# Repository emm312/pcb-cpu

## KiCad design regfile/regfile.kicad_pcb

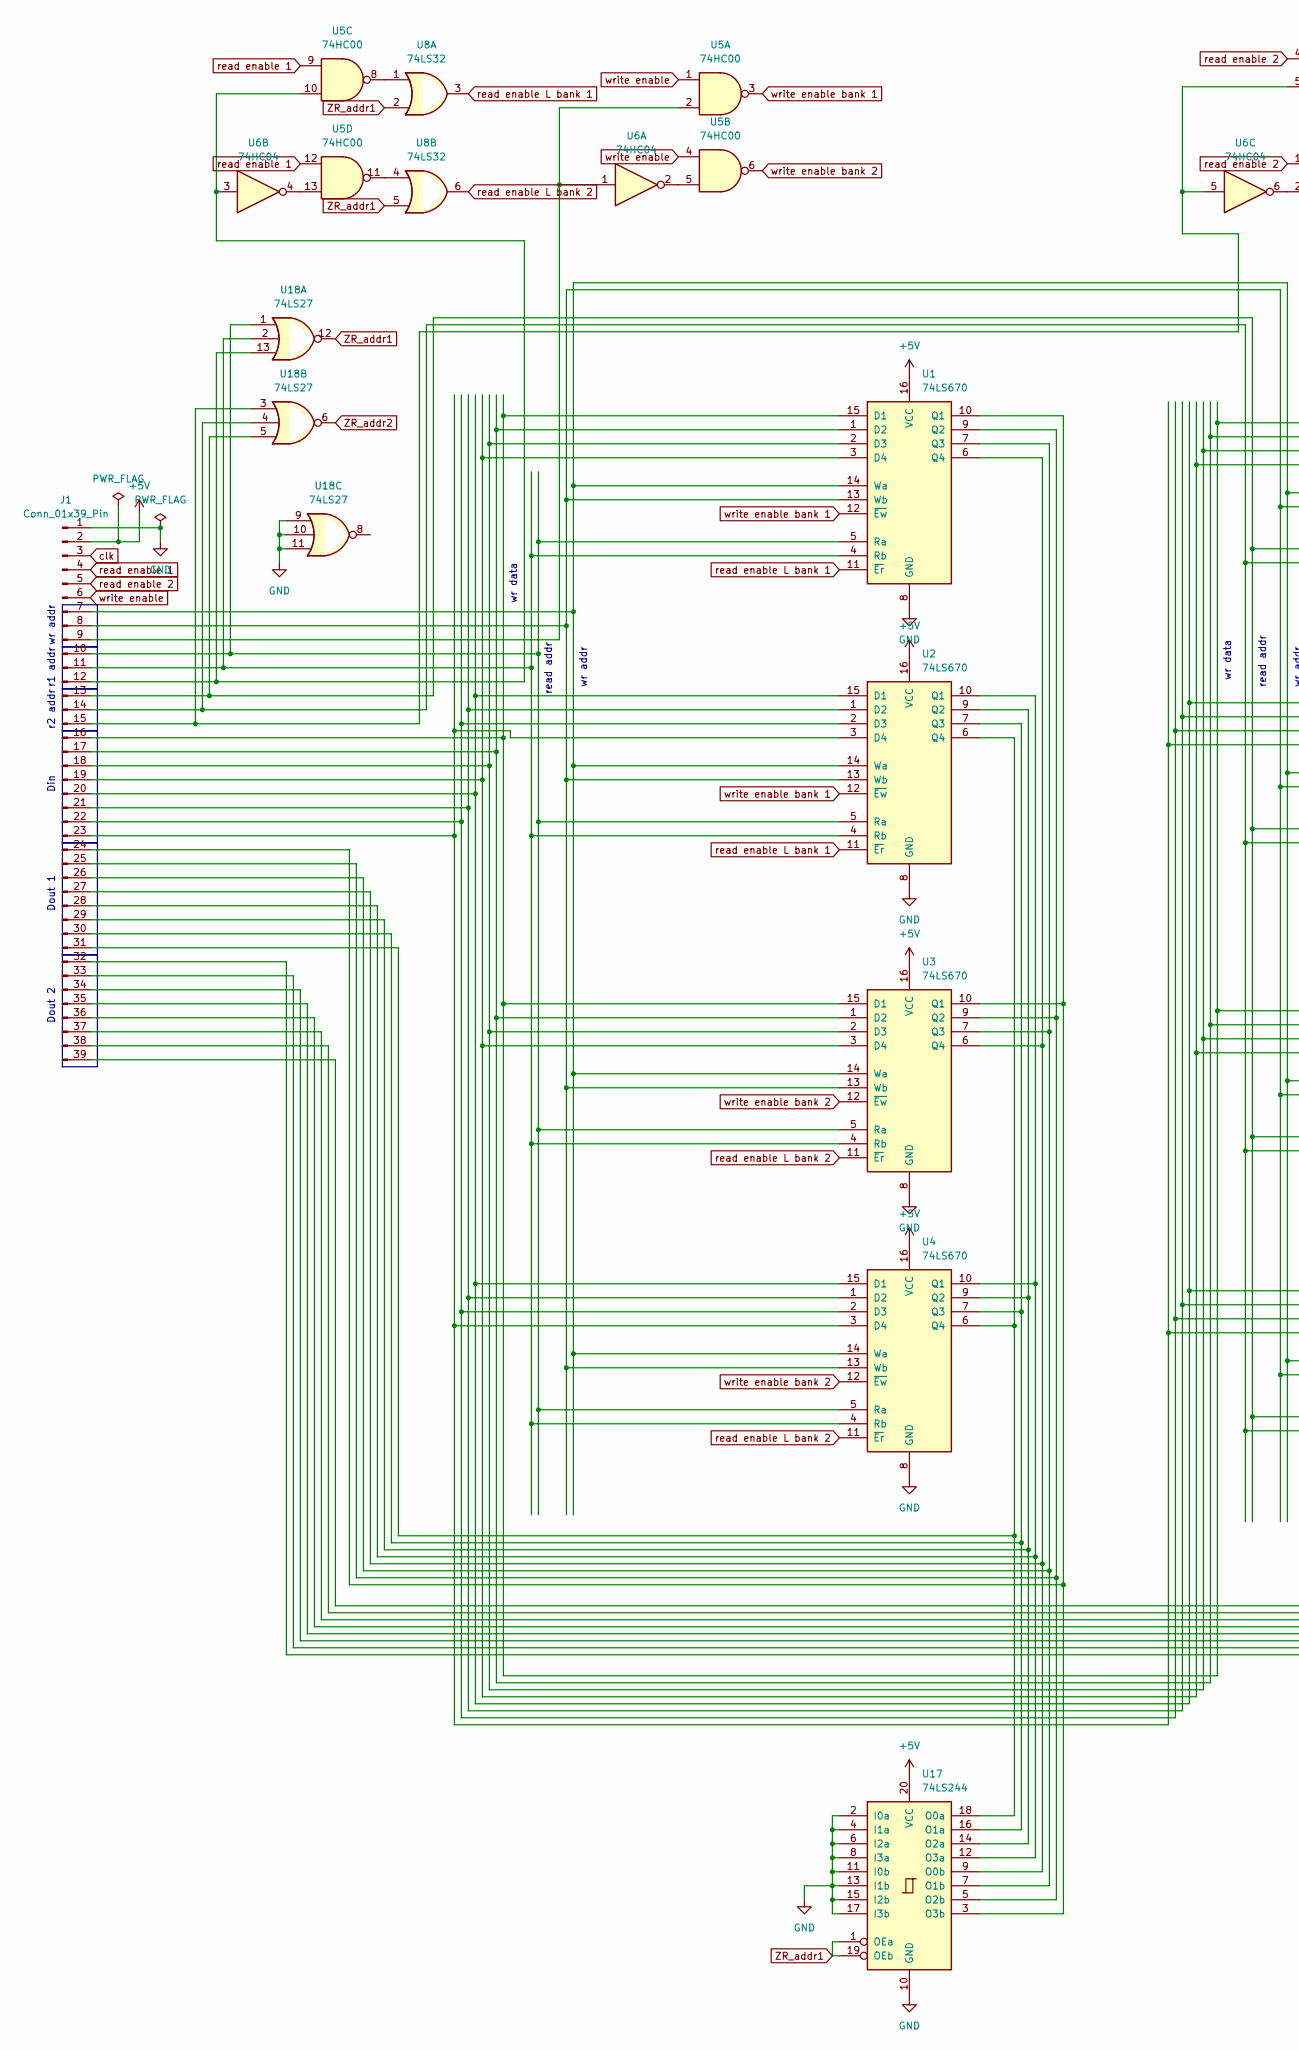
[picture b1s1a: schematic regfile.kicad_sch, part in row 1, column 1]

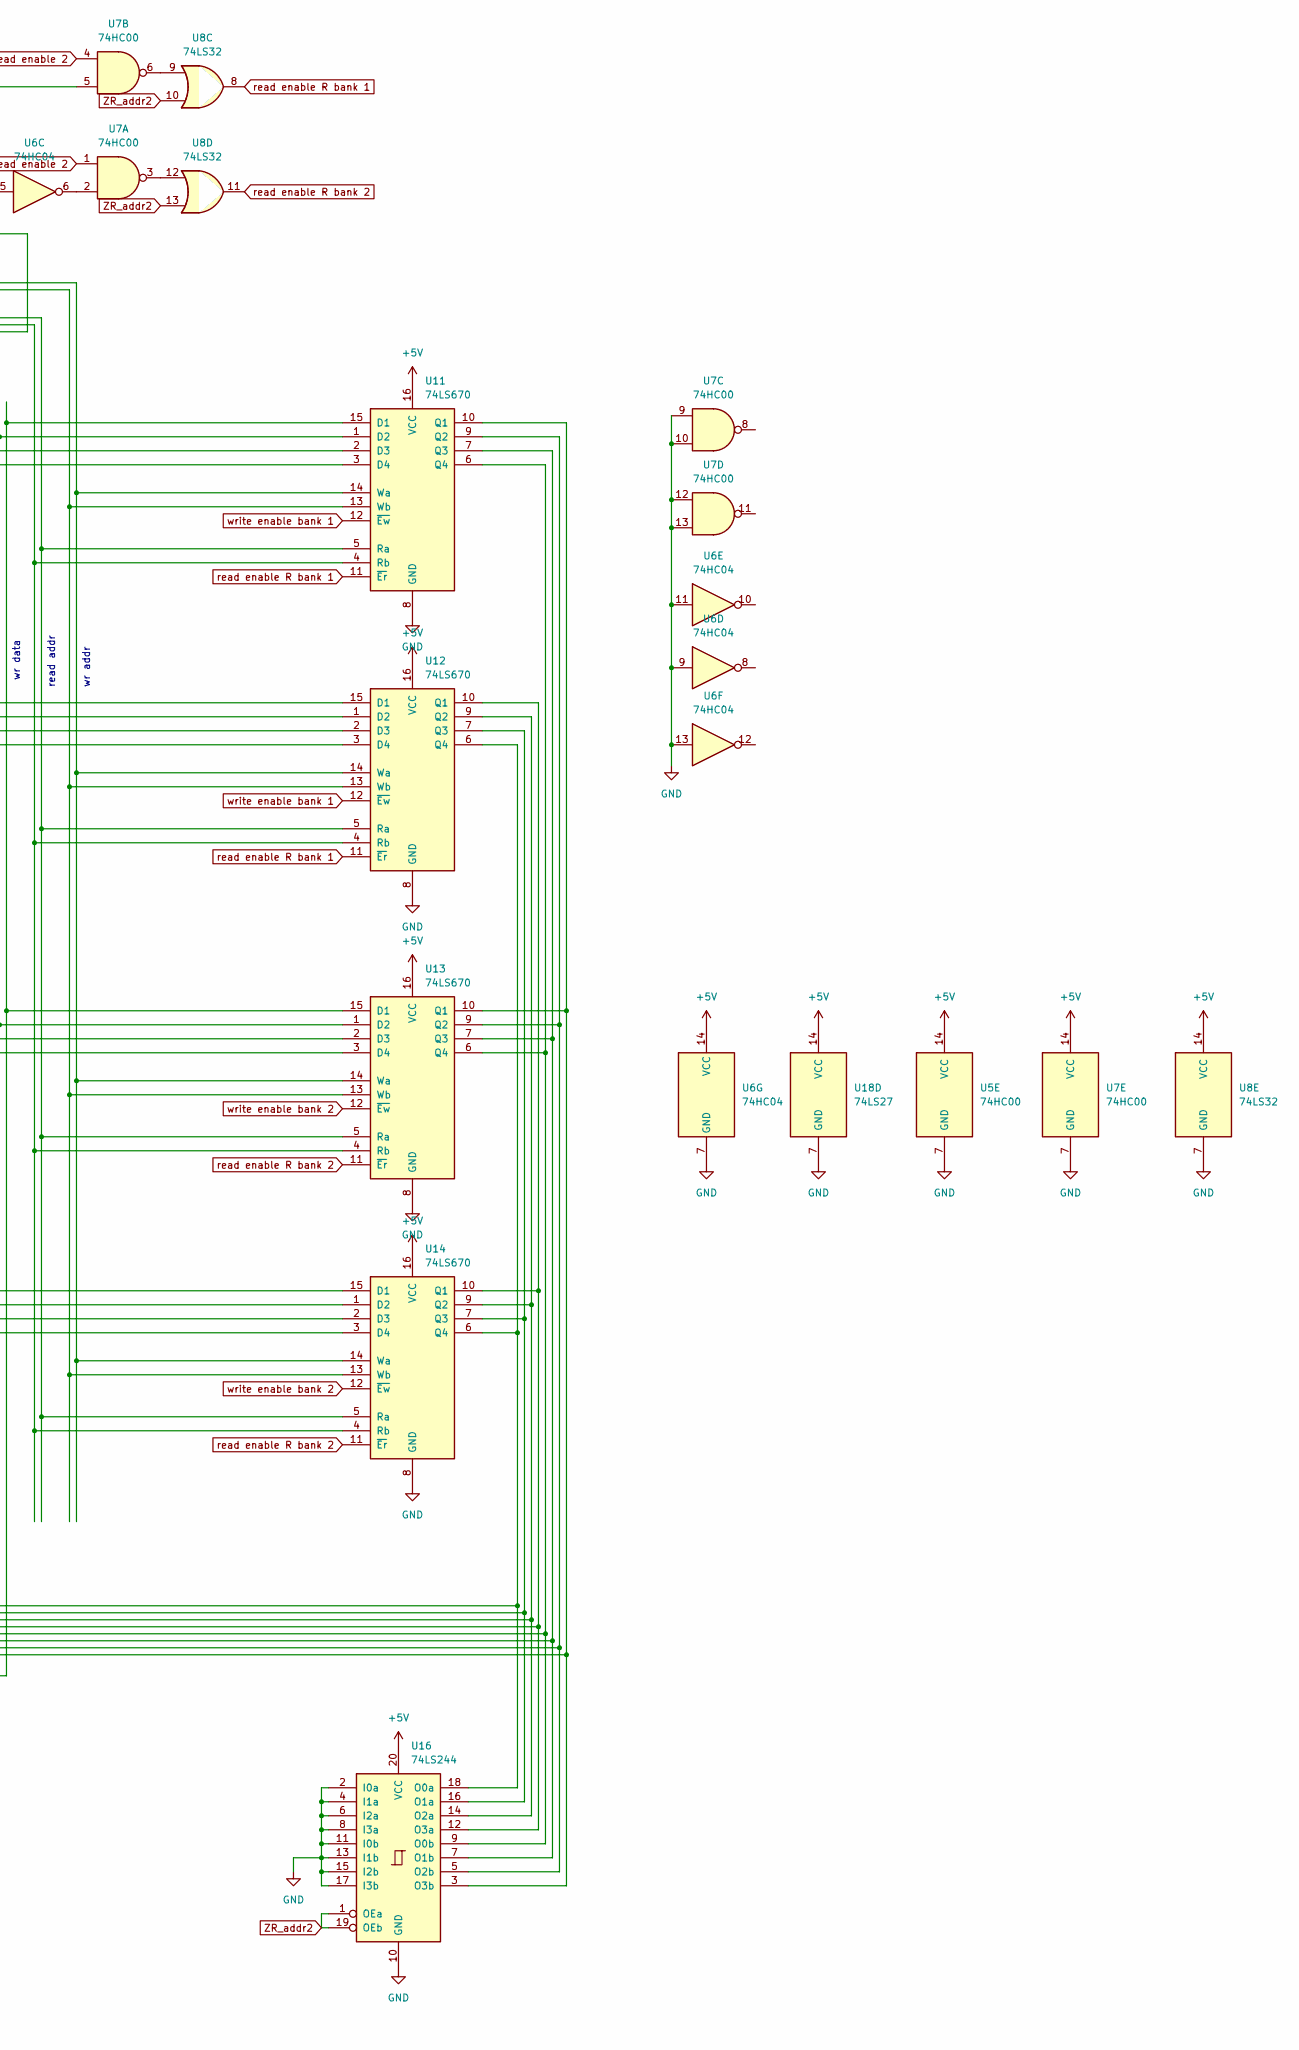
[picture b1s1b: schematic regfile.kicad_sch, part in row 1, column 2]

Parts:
J1: Conn_01x39_Pin; PinHeader_1x39_P2.54mm_Horizontal
U1, U2, U3, U4, U11, U12, U13, U14: 74LS670; DIP-16_W7.62mm
U5, U7: 74HC00; DIP-14_W7.62mm
U6: 74HC04; DIP-14_W7.62mm
U8: 74LS32; DIP-14_W7.62mm
U16, U17: 74LS244; DIP-20_W7.62mm
U18: 74LS27; DIP-14_W7.62mm

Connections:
+5V: J1.2, U1.16 (VCC), U2.16 (VCC), U3.16 (VCC), U4.16 (VCC), U5.14 (VCC), U6.14 (VCC), U7.14 (VCC), U8.14 (VCC), U11.16 (VCC), U12.16 (VCC), U13.16 (VCC), U14.16 (VCC), U16.20 (VCC), U17.20 (VCC), U18.14 (VCC)
GND: J1.1, U1.8 (GND), U2.8 (GND), U3.8 (GND), U4.8 (GND), U5.7 (GND), U6.7 (GND), U6.9, U6.11, U6.13, U7.7 (GND), U7.9, U7.10, U7.12, U7.13, U8.7 (GND), U11.8 (GND), U12.8 (GND), U13.8 (GND), U14.8 (GND), U16.2 (I0a), U16.4 (I1a), U16.6 (I2a), U16.8 (I3a), U16.10 (GND), U16.11 (I0b), U16.13 (I1b), U16.15 (I2b), U16.17 (I3b), U17.2 (I0a), U17.4 (I1a), U17.6 (I2a), U17.8 (I3a), U17.10 (GND), U17.11 (I0b), U17.13 (I1b), U17.15 (I2b), U17.17 (I3b), U18.7 (GND), U18.9, U18.10, U18.11
unnamed: J1.7, U1.14 (Wa), U2.14 (Wa), U3.14 (Wa), U4.14 (Wa), U11.14 (Wa), U12.14 (Wa), U13.14 (Wa), U14.14 (Wa)
unnamed: J1.8, U1.13 (Wb), U2.13 (Wb), U3.13 (Wb), U4.13 (Wb), U11.13 (Wb), U12.13 (Wb), U13.13 (Wb), U14.13 (Wb)
unnamed: J1.9, U5.2, U6.1
unnamed: J1.10, U1.5 (Ra), U2.5 (Ra), U3.5 (Ra), U4.5 (Ra), U18.1
unnamed: J1.11, U1.4 (Rb), U2.4 (Rb), U3.4 (Rb), U4.4 (Rb), U18.2
unnamed: J1.12, U5.10, U6.3, U18.13
unnamed: J1.13, U11.5 (Ra), U12.5 (Ra), U13.5 (Ra), U14.5 (Ra), U18.5
unnamed: J1.14, U11.4 (Rb), U12.4 (Rb), U13.4 (Rb), U14.4 (Rb), U18.4
unnamed: J1.15, U6.5, U7.5, U18.3
unnamed: J1.16, U1.15 (D1), U3.15 (D1), U11.15 (D1), U13.15 (D1)
unnamed: J1.17, U1.1 (D2), U3.1 (D2), U11.1 (D2), U13.1 (D2)
unnamed: J1.18, U1.2 (D3), U3.2 (D3), U11.2 (D3), U13.2 (D3)
unnamed: J1.19, U1.3 (D4), U3.3 (D4), U11.3 (D4), U13.3 (D4)
unnamed: J1.20, U2.15 (D1), U4.15 (D1), U12.15 (D1), U14.15 (D1)
unnamed: J1.21, U2.1 (D2), U4.1 (D2), U12.1 (D2), U14.1 (D2)
unnamed: J1.22, U2.2 (D3), U4.2 (D3), U12.2 (D3), U14.2 (D3)
unnamed: J1.23, U2.3 (D4), U4.3 (D4), U12.3 (D4), U14.3 (D4)
unnamed: J1.24, U1.10 (Q1), U3.10 (Q1), U17.3 (O3b)
unnamed: J1.25, U1.9 (Q2), U3.9 (Q2), U17.5 (O2b)
unnamed: J1.26, U1.7 (Q3), U3.7 (Q3), U17.7 (O1b)
unnamed: J1.27, U1.6 (Q4), U3.6 (Q4), U17.9 (O0b)
unnamed: J1.28, U2.10 (Q1), U4.10 (Q1), U17.12 (O3a)
unnamed: J1.29, U2.9 (Q2), U4.9 (Q2), U17.14 (O2a)
unnamed: J1.30, U2.7 (Q3), U4.7 (Q3), U17.16 (O1a)
unnamed: J1.31, U2.6 (Q4), U4.6 (Q4), U17.18 (O0a)
unnamed: J1.32, U11.10 (Q1), U13.10 (Q1), U16.3 (O3b)
unnamed: J1.33, U11.9 (Q2), U13.9 (Q2), U16.5 (O2b)
unnamed: J1.34, U11.7 (Q3), U13.7 (Q3), U16.7 (O1b)
unnamed: J1.35, U11.6 (Q4), U13.6 (Q4), U16.9 (O0b)
unnamed: J1.36, U12.10 (Q1), U14.10 (Q1), U16.12 (O3a)
unnamed: J1.37, U12.9 (Q2), U14.9 (Q2), U16.14 (O2a)
unnamed: J1.38, U12.7 (Q3), U14.7 (Q3), U16.16 (O1a)
unnamed: J1.39, U12.6 (Q4), U14.6 (Q4), U16.18 (O0a)
unnamed: U5.5, U6.2
unnamed: U5.8, U8.1
unnamed: U5.11, U8.4
unnamed: U5.13, U6.4
unnamed: U6.6, U7.2
unnamed: U7.3, U8.12
unnamed: U7.6, U8.9
ZR_addr1: U8.2, U8.5, U17.1 (OEa), U17.19 (OEb), U18.12
ZR_addr2: U8.10, U8.13, U16.1 (OEa), U16.19 (OEb), U18.6
clk: J1.3
read enable 1: J1.4, U5.9, U5.12
read enable 2: J1.5, U7.1, U7.4
read enable L bank 1: U1.11 (~Er), U2.11 (~Er), U8.3
read enable L bank 2: U3.11 (~Er), U4.11 (~Er), U8.6
read enable R bank 1: U8.8, U11.11 (~Er), U12.11 (~Er)
read enable R bank 2: U8.11, U13.11 (~Er), U14.11 (~Er)
write enable: J1.6, U5.1, U5.4
write enable bank 1: U1.12 (~Ew), U2.12 (~Ew), U5.3, U11.12 (~Ew), U12.12 (~Ew)
write enable bank 2: U3.12 (~Ew), U4.12 (~Ew), U5.6, U13.12 (~Ew), U14.12 (~Ew)

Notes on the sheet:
Dout 1
Din
Dout 2
read addr
wr addr
r2 addr
wr data
r1 addr

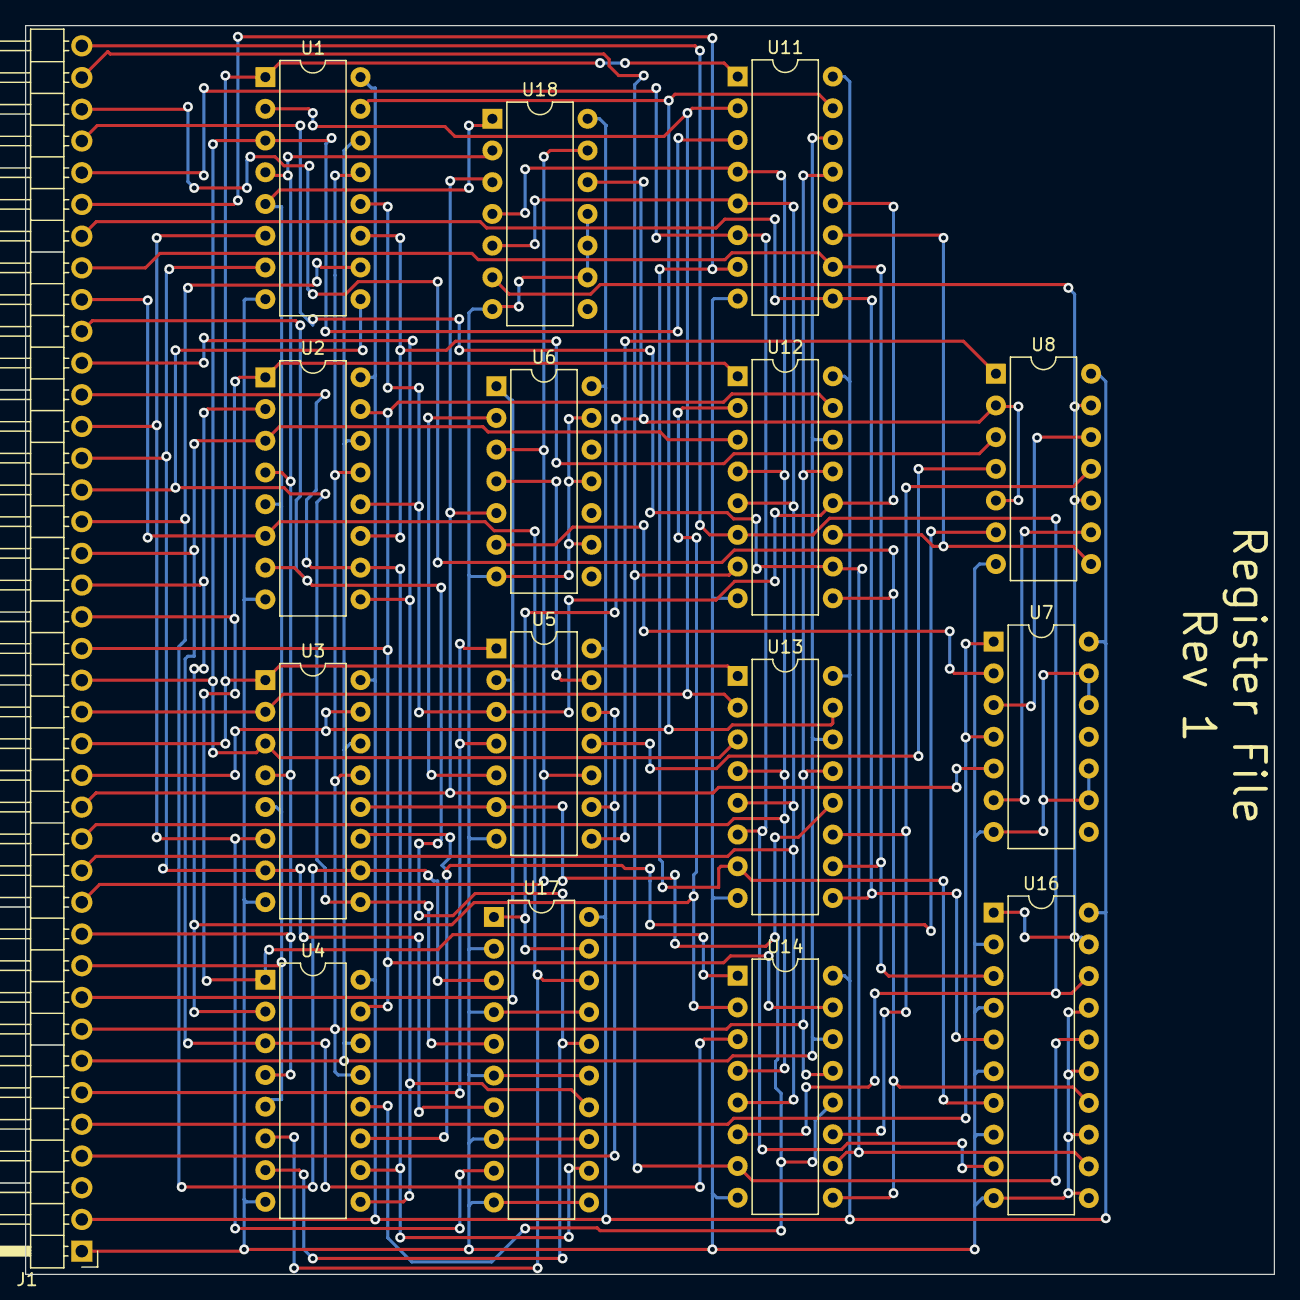
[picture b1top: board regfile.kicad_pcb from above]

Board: 2 copper layers, 100.0 x 100.0 mm, 16 parts (0 on the bottom side), 53 nets.

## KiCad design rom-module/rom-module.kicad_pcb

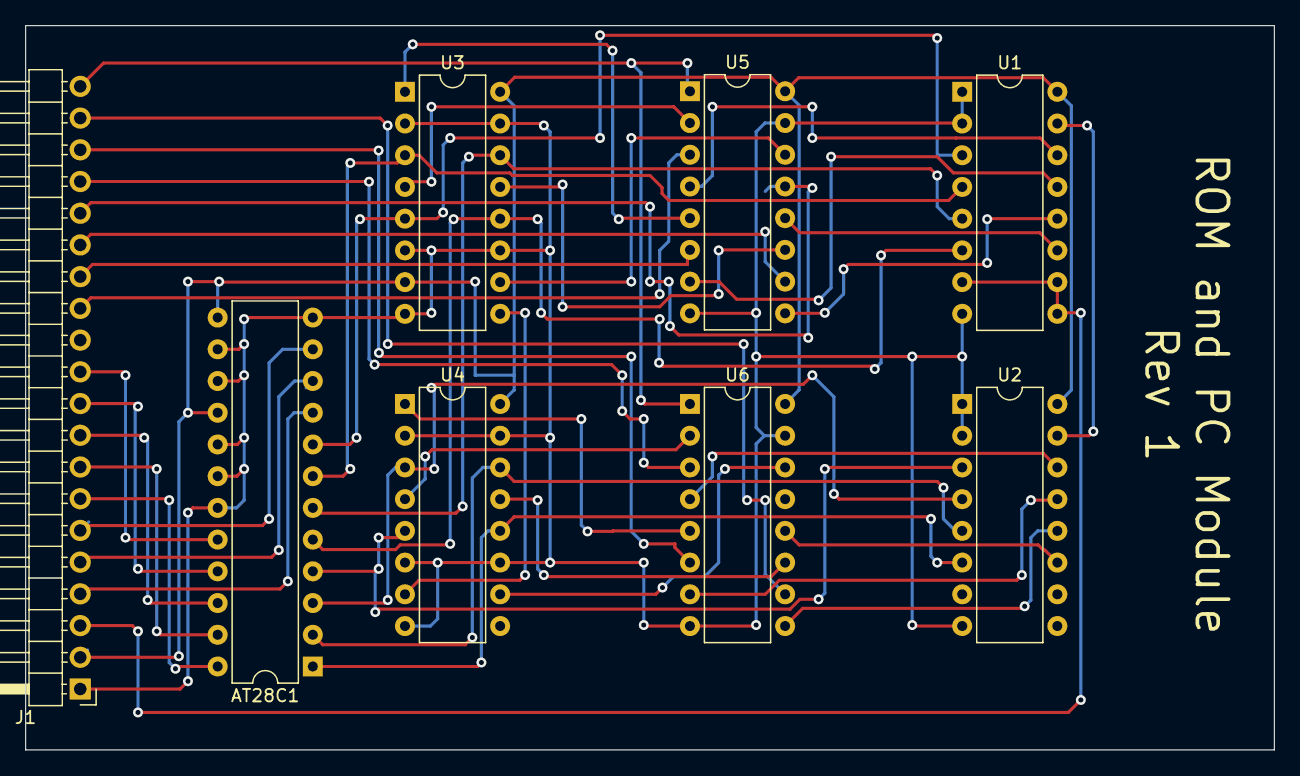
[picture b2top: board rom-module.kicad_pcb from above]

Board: 2 copper layers, 100.0 x 58.0 mm, 8 parts (0 on the bottom side), 45 nets.

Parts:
AT28C1: DIP-24_W7.62mm
J1: Conn_01x20_Pin; PinHeader_1x20_P2.54mm_Horizontal
U1, U2: 74HC173; DIP-16_W7.62mm
U3, U4: 74HC283; DIP-16_W7.62mm
U5, U6: 74LS157; DIP-16_W7.62mm

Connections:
+5V: AT28C1.13 (VCC), AT28C1.16 (!WE), J1.2, U1.16 (VCC), U2.16 (VCC), U3.7 (C0), U3.16 (VCC), U4.16 (VCC), U5.16 (VCC), U6.16 (VCC)
GND: AT28C1.12 (GND), AT28C1.14 (A8), AT28C1.15 (A9), AT28C1.17 (!OE), AT28C1.18 (A10), AT28C1.19 (!CE), J1.1, U1.1 (Oe1), U1.2 (Oe2), U1.8 (GND), U2.1 (Oe1), U2.2 (Oe2), U2.8 (GND), U3.2 (B2), U3.6 (B1), U3.8 (GND), U3.11 (B4), U3.15 (B3), U4.2 (B2), U4.6 (B1), U4.8 (GND), U4.11 (B4), U4.15 (B3), U5.8 (GND), U5.15 (E), U6.8 (GND), U6.15 (E)
unnamed: AT28C1.8 (A0), U1.3 (Q0), U3.5 (A1)
unnamed: AT28C1.7 (A1), U1.4 (Q1), U3.3 (A2)
unnamed: AT28C1.6 (A2), U1.5 (Q2), U3.14 (A3)
unnamed: AT28C1.5 (A3), U1.6 (Q3), U3.12 (A4)
unnamed: AT28C1.4 (A4), U2.3 (Q0), U4.5 (A1)
unnamed: AT28C1.3 (A5), U2.4 (Q1), U4.3 (A2)
unnamed: AT28C1.2 (A6), U2.5 (Q2), U4.14 (A3)
unnamed: AT28C1.1 (A7), U2.6 (Q3), U4.12 (A4)
unnamed: AT28C1.9 (IO0), J1.4
unnamed: AT28C1.10 (IO1), J1.5
unnamed: AT28C1.11 (IO2), J1.6
unnamed: AT28C1.24 (IO3), J1.7
unnamed: AT28C1.23 (IO4), J1.8
unnamed: AT28C1.22 (IO5), J1.9
unnamed: AT28C1.21 (IO6), J1.10
unnamed: AT28C1.20 (IO7), J1.11
unnamed: J1.13, U5.3 (I1a)
unnamed: J1.14, U5.6 (I1b)
unnamed: J1.15, U5.10 (I1c)
unnamed: J1.16, U5.13 (I1d)
unnamed: J1.17, U6.3 (I1a)
unnamed: J1.18, U6.6 (I1b)
unnamed: J1.19, U6.10 (I1c)
unnamed: U1.14 (D0), U5.4 (Za)
unnamed: U1.13 (D1), U5.7 (Zb)
unnamed: U1.12 (D2), U5.9 (Zc)
unnamed: U1.11 (D3), U5.12 (Zd)
unnamed: U2.14 (D0), U6.4 (Za)
unnamed: U2.13 (D1), U6.7 (Zb)
unnamed: U2.12 (D2), U6.9 (Zc)
unnamed: U2.11 (D3), U6.12 (Zd)
unnamed: U3.9 (C4), U4.7 (C0)
unnamed: U3.4 (S1), U5.2 (I0a)
unnamed: U3.1 (S2), U5.5 (I0b)
unnamed: U3.13 (S3), U5.11 (I0c)
unnamed: U3.10 (S4), U5.14 (I0d)
unnamed: U4.4 (S1), U6.2 (I0a)
unnamed: U4.1 (S2), U6.5 (I0b)
unnamed: U4.13 (S3), U6.11 (I0c)
unnamed: U4.10 (S4), U6.14 (I0d)
br_en: J1.20, U5.1 (S), U6.1 (S)
clk: J1.3, U1.7 (Cp), U1.9 (E1), U1.10 (E2)
rst: U1.15 (Mr), U2.15 (Mr)

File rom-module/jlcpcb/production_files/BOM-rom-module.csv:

Comment,Designator,Footprint,LCSC
74HC283,U4,DIP-16_W7.62mm,
74LS157,U6,DIP-16_W7.62mm,
74LS157,U5,DIP-16_W7.62mm,
74HC283,U3,DIP-16_W7.62mm,
74HC173,U2,DIP-16_W7.62mm,
74HC173,U1,DIP-16_W7.62mm,
Conn_01x20_Pin,J1,PinHeader_1x20_P2.54mm_Horizontal,
~,AT28C1,DIP-24_W7.62mm,

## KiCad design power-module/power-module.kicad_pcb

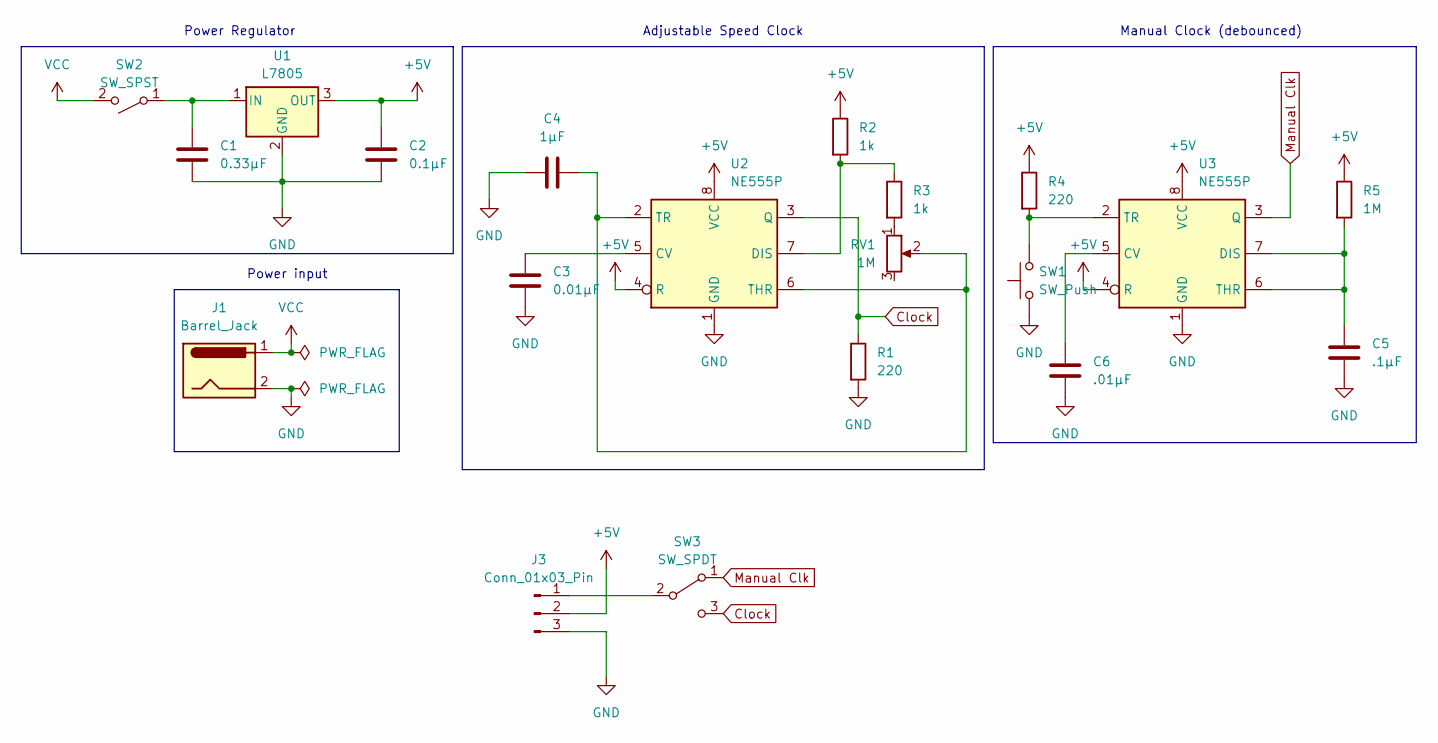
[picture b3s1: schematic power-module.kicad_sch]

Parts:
C1: 0.33μF; C_Radial_D4.0mm_H7.0mm_P1.50mm
C2: 0.1μF; C_Radial_D4.0mm_H7.0mm_P1.50mm
C3: 0.01μF; C_Radial_D4.0mm_H7.0mm_P1.50mm
C4: 1μF; C_Radial_D4.0mm_H7.0mm_P1.50mm
C5: .1μF; C_Radial_D4.0mm_H7.0mm_P1.50mm
C6: .01μF; C_Radial_D4.0mm_H7.0mm_P1.50mm
J1: Barrel_Jack; BarrelJack_SwitchcraftConxall_RAPC10U_Horizontal
J3: Conn_01x03_Pin; PinHeader_1x03_P2.54mm_Horizontal
R1, R4: 220; R_Axial_DIN0207_L6.3mm_D2.5mm_P10.16mm_Horizontal
R2, R3: 1k; R_Axial_DIN0207_L6.3mm_D2.5mm_P10.16mm_Horizontal
R5: 1M; R_Axial_DIN0207_L6.3mm_D2.5mm_P10.16mm_Horizontal
RV1: 1M; Potentiometer_ACP_CA9-V10_Vertical_Hole
SW1: SW_Push; SW_PUSH_6mm
SW2: SW_SPST; SW_DIP_SPSTx01_Slide_9.78x4.72mm_W7.62mm_P2.54mm
SW3: SW_SPDT; SW_Slide_1P2T_CK_OS102011MS2Q
U1: L7805; TO-220-3_Vertical
U2, U3: NE555P; DIP-8_W7.62mm

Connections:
+5V: C2.1, J3.2, R2.1, R4.1, R5.1, U1.3 (OUT), U2.4 (R), U2.8 (VCC), U3.4 (R), U3.8 (VCC)
Clock: R1.1, SW3.3 (C), U2.3 (Q)
GND: C1.2, C2.2, C3.2, C4.1, C5.2, C6.2, J1.2, J3.3, R1.2, SW1.1, U1.2 (GND), U2.1 (GND), U3.1 (GND)
Manual Clk: SW3.1 (A), U3.3 (Q)
unnamed: J3.1, SW3.2 (B)
unnamed: R3.2, RV1.1
unnamed: C1.1, SW2.1 (A), U1.1 (IN)
unnamed: C3.1, U2.5 (CV)
unnamed: R2.2, R3.1, U2.7 (DIS)
unnamed: C4.2, RV1.2, U2.2 (TR), U2.6 (THR)
unnamed: C6.1, U3.5 (CV)
unnamed: C5.1, R5.2, U3.6 (THR), U3.7 (DIS)
unnamed: R4.2, SW1.2, U3.2 (TR)
VCC: J1.1, SW2.2 (B)

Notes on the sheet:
Power Regulator
Manual Clock (debounced)
Adjustable Speed Clock
Power input

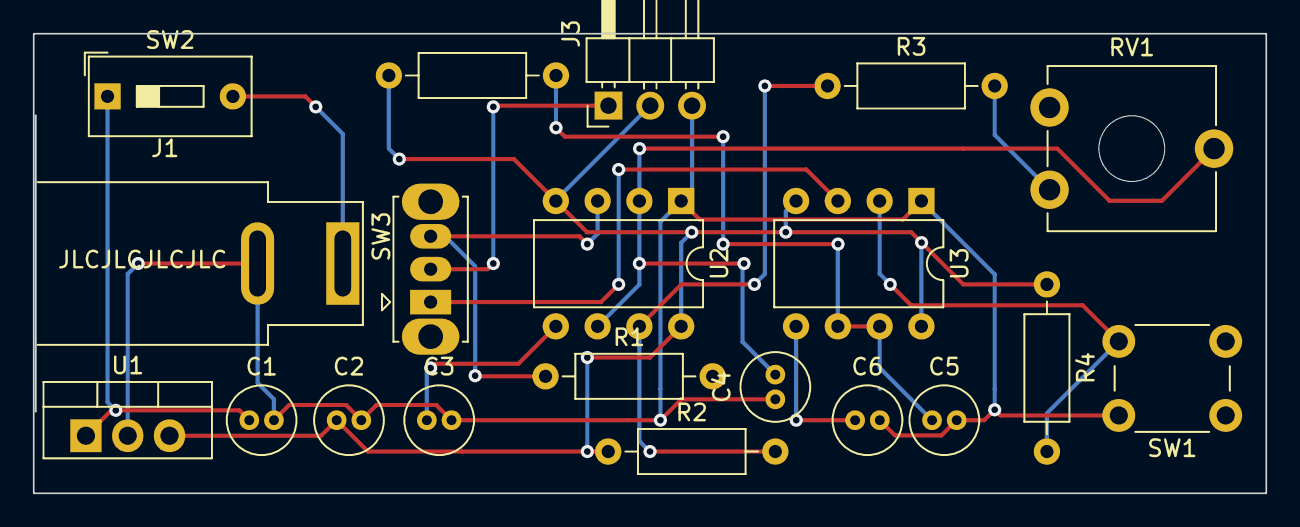
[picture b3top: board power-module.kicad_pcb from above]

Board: 2 copper layers, 74.9 x 27.9 mm, 20 parts (0 on the bottom side), 14 nets.

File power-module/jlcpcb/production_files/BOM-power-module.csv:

Comment,Designator,Footprint,LCSC
1μF,C4,C_Radial_D4.0mm_H7.0mm_P1.50mm,
.1μF,C5,C_Radial_D4.0mm_H7.0mm_P1.50mm,
220,R1,R_Axial_DIN0207_L6.3mm_D2.5mm_P10.16mm_Horizontal,
1M,RV1,Potentiometer_ACP_CA9-V10_Vertical_Hole,
Barrel_Jack,J1,BarrelJack_SwitchcraftConxall_RAPC10U_Horizontal,
SW_SPDT,SW3,SW_Slide_1P2T_CK_OS102011MS2Q,
1k,R3,R_Axial_DIN0207_L6.3mm_D2.5mm_P10.16mm_Horizontal,
.01μF,C6,C_Radial_D4.0mm_H7.0mm_P1.50mm,
NE555P,U3,DIP-8_W7.62mm,
0.01μF,C3,C_Radial_D4.0mm_H7.0mm_P1.50mm,
NE555P,U2,DIP-8_W7.62mm,
1M,R5,R_Axial_DIN0207_L6.3mm_D2.5mm_P10.16mm_Horizontal,
0.33μF,C1,C_Radial_D4.0mm_H7.0mm_P1.50mm,
SW_Push,SW1,SW_PUSH_6mm,
Conn_01x03_Pin,J3,PinHeader_1x03_P2.54mm_Horizontal,
1k,R2,R_Axial_DIN0207_L6.3mm_D2.5mm_P10.16mm_Horizontal,
220,R4,R_Axial_DIN0207_L6.3mm_D2.5mm_P10.16mm_Horizontal,
0.1μF,C2,C_Radial_D4.0mm_H7.0mm_P1.50mm,
L7805,U1,TO-220-3_Vertical,
SW_SPST,SW2,SW_DIP_SPSTx01_Slide_9.78x4.72mm_W7.62mm_P2.54mm,

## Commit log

2024-01-28 init
2024-01-29 add some thingies
2024-01-29 dwadwdawdaw
2024-02-02 fix logic for the regfile
2024-02-02 footprints
2024-02-02 finish regfile
